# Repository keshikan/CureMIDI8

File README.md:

# USB-MIDI Interface (8IN/8OUT) for STM32 "CureMIDI8"

## Overview (概要)

This repository shows STM32F7 (ARM Cortex-M7) based  8IN/8OUT USB-MIDI Interface.
It is USB MIDI class-compliant, so you can add MIDI port without drivers(Windows, iOS, Android, etc...)

The USB-MIDI Class Driver is based on [mimuz-tuch](https://github.com/mimuz/mimuz-tuch) project (c) [D.F.Mac. @TripArts Music](https://github.com/tadfmac).

STM32F7を使用した、USB-MIDIインターフェースです。INを8系統、OUTを8系統実装しています。USB MIDI Classに対応するシステム(Windows, iOS, Android, etc.)に対し、ドライバレスでMIDI入出力ポートを追加できます。

USB MIDI Classドライバは、[D.F.Mac. @TripArts Music](https://github.com/tadfmac)氏作成の[ドライバ](https://github.com/mimuz/mimuz-tuch/tree/master/STM32)を元に、I/F部(usbd_midi_if.c/h)の改造を行っています。

## Specifications (特徴)

* High-Speed MCU (STM32F722VCT)
* USB MIDI class-compliant
* MIDI port: 8IN/8OUT
* MIDI buffer size: 2kB * (8IN+8OUT) = 32kB

## Building Information (ビルド方法)

### Making hardware

See [Schematic](./hardware/schematic.pdf), [KiCad Source](./hardware/kicad_source).
CureMIDI8 consist of a mainboard and a MIDI-IN board.

回路図は[こちら](./hardware/schematic.pdf).
CureMIDI8は、メイン基板(Mainboard)と、拡張基板(MIDI-IN board)に分かれています。

### Building software

Install [STM32CubeIDE](https://www.st.com/ja/development-tools/stm32cubeide.html), import [Project files](./software/CubeIDE_project/). If you have successfully imported, you can build the project without error and the binary file will be created in /CubeIDE_project/Debug/.

[STM32CubeIDE](https://www.st.com/ja/development-tools/stm32cubeide.html)をインストールし、[プロジェクトファイル](./software/CubeIDE_project/)をインポートして下さい。インポートに成功していれば、STM32CubeIDE上でプロジェクトをビルドするだけで、/SW4STM32_project/Debug/フォルダにバイナリファイルが生成されるはずです。

## How to Porting (ポーティング方法)

### CubeIDE Project (recommended)

Refer to [here](software/README.md). (written in Japanese)

[こちら](software/README.md)を参照して下さい。

### SW4STM32 Project

(Older Information)
Load CureMIDI8.ioc on [STM32CubeMX (Ver.5.0.1)](https://www.st.com/ja/development-tools/stm32cubemx.html), change the pin assignment, and generate code.
After code generation, copy usb device driver as described below. You can use ./click_after_code_generation.bat (in Windows).

(以下は古い情報です)
CureMIDI8.iocを[STM32CubeMX (Ver.5.0.1)](https://www.st.com/ja/development-tools/stm32cubemx.html)で読みこみ、ポートを適宜修正し、コード生成をして下さい。コードを生成後、./template下のUSBドライバを、下記の通り上書きして下さい。上書きは、./click_after_code_generation.batを実行してもOKです。

* ./template/\*.c => ./Src/\*.c
* ./template/\*.h => ./Inc/\*.h

## File Location (ファイルの場所)

* [Binary file for STM32F722](./software/bin/)
* [STM32CubeIDE + STM32CubeMX(6.1.1) Project file](./software/CubeIDE_Project/)
* [SW4STM32 + STM32CubeMX(5.0.1) Project file](./software/SW4STM32_project/)
* [Schematic](./hardware/schematic.pdf)

## NOTICE (注意)

### VID/PID

Vendor ID(VID) and Product ID(PID) in <usbd_desc.c> should be unique pair for each USB devices.
Default VID 0x1209 and PID 0x0001 is experimental IDs from [http://pid.codes](http://pid.codes) .When distributing or selling, you must get your own IDs, and change to your own IDs in order to avoid conflicting to other USB devices.

USBのVendor ID(VID)とProduct ID(PID)は、<usbd_desc.c>内に記述します。
デフォルトのVID(0x1209)/PID(0x0001)ペアは、[http://pid.codes](http://pid.codes)で定められている実験用IDです。そのため、本機器を配布したり販売したりする場合には、別途固有のIDペアを取得し、書き換えてご使用いただく必要があります。

## References (参考情報)

### MIDI specification

* [The Complete MIDI 1.0 Detailed Specification](https://www.midi.org/specifications/item/the-midi-1-0-specification) ([MIDI Association](https://www.midi.org/))
* [MIDI1.0規格書](http://amei.or.jp/midistandardcommittee/MIDI1.0.pdf) ([AMEI](http://amei.or.jp/))
* [MIDIの学習](http://www1.plala.or.jp/yuuto/midi/index.html) ([Laboratory "U"](http://www1.plala.or.jp/yuuto/top.html))

### USB-MIDI technical information

* [Universal Serial Bus Device Class Definition for MIDI Devices](http://www.usb.org/developers/docs/devclass_docs/midi10.pdf)
* [USBおよびUSB MIDIについて調べる](http://picmidi.seesaa.net/article/150728556.html) ([PICでMIDI！](http://picmidi.seesaa.net/))

## Copyrights (著作権)

* USB MIDI Class Driver by [D.F.Mac. @TripArts Music](http://ta-music.strikingly.com/)
* STM32 CubeF7 by [STMicroelectronics](https://www.st.com/en/embedded-software/stm32cubef7.html)

## Author (著者)

(c) 2019 Keshikan ( [Website](http://www.keshikan.net/),  [Twitter](https://twitter.com/keshinomi_88pro) )

## License (ライセンス)

* USB MIDI Class Driver: [CC BY 4.0](https://creativecommons.org/licenses/by/4.0/)
* STM32 CubeF7: BSD-3-Clause based.
* Other Codes, Hardware, Schematic: [GPLv3](https://www.gnu.org/licenses/gpl-3.0.html)

See also [LICENSE.md](./LICENSE.md)

## Update History (更新履歴)

* (2021/02/14)
  * Added STM32CubeIDE(1.5.1) + CubeMX(6.1.1) Project.
* (2019/01/14)
  * Initial Release.

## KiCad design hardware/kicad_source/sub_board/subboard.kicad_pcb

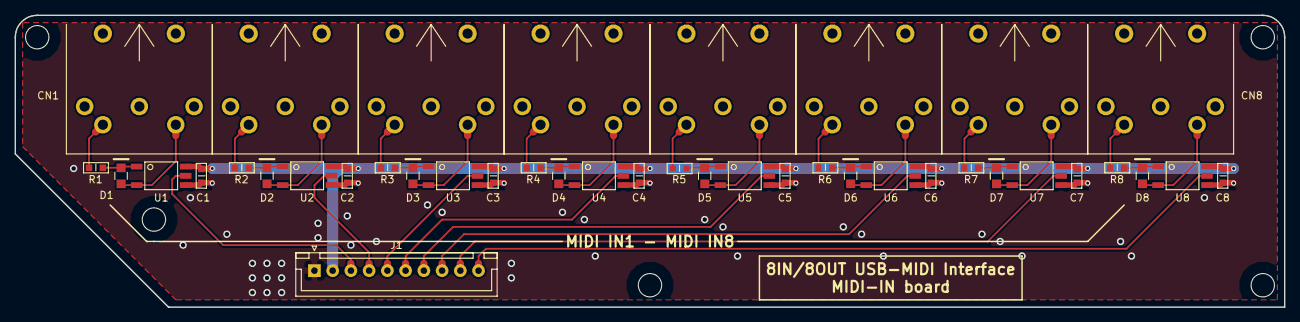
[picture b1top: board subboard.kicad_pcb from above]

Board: 2 copper layers, 174.0 x 40.0 mm, 41 parts (0 on the bottom side), 34 nets.

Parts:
C1, C2, C3, C4, C5, C6, C7, C8: 0.1μF; SMD_0603(1608)
CN1, CN2, CN3, CN4, CN5, CN6, CN7, CN8: DIN_5; DIN_5P_MIDI
D1, D2, D3, D4, D5, D6, D7, D8: D_Small; SMD_0805(2012)_polar
J1: Conn_01x10; JST_XH_B10B-XH-A_10x2.50mm_Straight
R1, R2, R3, R4, R5, R6, R7, R8: 220; SMD_0603(1608)
U1, U2, U3, U4, U5, U6, U7, U8: TLP2361; 11-4L1S(TLP2361)

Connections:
IN_1: J1.3, U1.5
IN_2: J1.4, U2.5
IN_3: J1.5, U3.5
IN_3V3: C1.1, C2.1, C3.1, C4.1, C5.1, C6.1, C7.1, C8.1, J1.2, U1.6, U2.6, U3.6, U4.6, U5.6, U6.6, U7.6, U8.6
IN_4: J1.6, U4.5
IN_5: J1.7, U5.5
IN_6: J1.8, U6.5
IN_7: J1.9, U7.5
IN_8: J1.10, U8.5
IN_GND: C1.2, C2.2, C3.2, C4.2, C5.2, C6.2, C7.2, C8.2, J1.1, U1.4, U2.4, U3.4, U4.4, U5.4, U6.4, U7.4, U8.4
unnamed: CN1.4, R1.1
unnamed: CN1.5, D1.2, U1.3
unnamed: CN2.4, R2.1
unnamed: CN2.5, D2.2, U2.3
unnamed: CN3.4, R3.1
unnamed: CN3.5, D3.2, U3.3
unnamed: CN4.4, R4.1
unnamed: CN4.5, D4.2, U4.3
unnamed: CN5.4, R5.1
unnamed: CN5.5, D5.2, U5.3
unnamed: CN6.4, R6.1
unnamed: CN6.5, D6.2, U6.3
unnamed: CN7.4, R7.1
unnamed: CN7.5, D7.2, U7.3
unnamed: CN8.4, R8.1
unnamed: CN8.5, D8.2, U8.3
unnamed: D1.1, R1.2, U1.1
unnamed: D2.1, R2.2, U2.1
unnamed: D3.1, R3.2, U3.1
unnamed: D4.1, R4.2, U4.1
unnamed: D5.1, R5.2, U5.1
unnamed: D6.1, R6.2, U6.1
unnamed: D7.1, R7.2, U7.1
unnamed: D8.1, R8.2, U8.1

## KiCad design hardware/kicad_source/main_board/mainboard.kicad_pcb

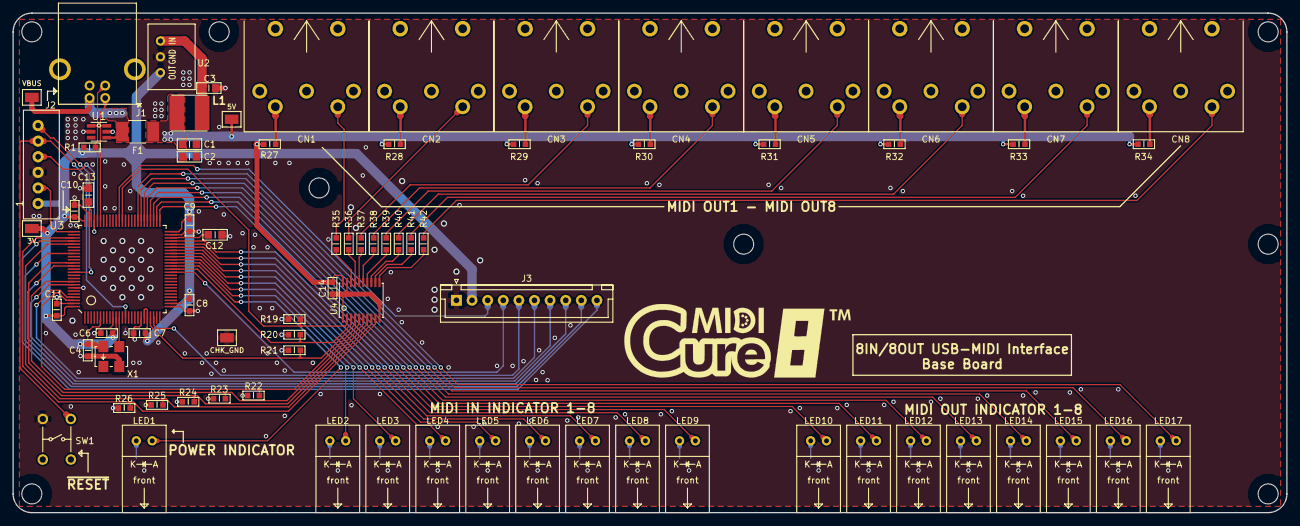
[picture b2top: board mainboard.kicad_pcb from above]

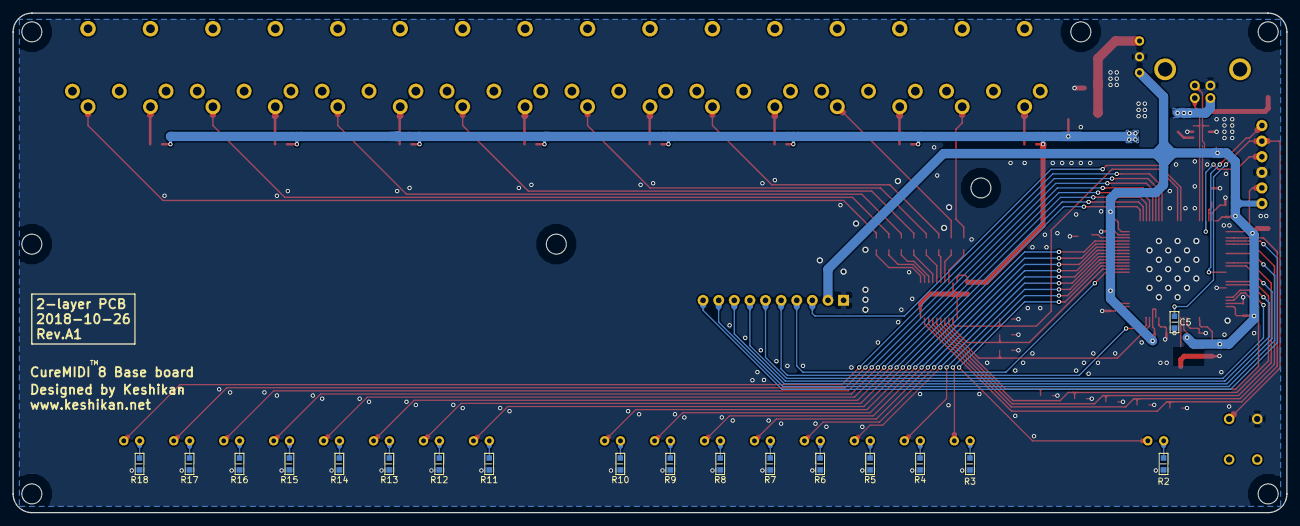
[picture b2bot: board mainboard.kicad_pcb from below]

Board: 2 copper layers, 204.0 x 80.0 mm, 96 parts (18 on the bottom side), 88 nets.

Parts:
C1, C2, C3, C12, C13: 4.7μF; SMD_0805(2012)
C4, C5, C6, C7, C8, C9, C10, C11, C14: 0.1μF; SMD_0603(1608)
CN1, CN2, CN3, CN4, CN5, CN6, CN7, CN8: DIN_5; DIN_5P_MIDI
F1: PolySW 0.35A; miniSMDC030F
J1: USB_B; USB_B_F
J2: CONN_01X06; XH-6P-TOP
J3: Conn_01x10; JST_XH_B10B-XH-A_10x2.50mm_Straight
L1: 10μH; Wurth_Elektronik_74477410
LED1, LED2, LED3, LED4, LED5, LED6, LED7, LED8, LED9, LED10, LED11, LED12, LED13, LED14, LED15, LED16, LED17: LED_Small; LEDSpacer_1low
P1: VBUS; CHK_Terminal_SMD
P2: 5V; CHK_Terminal_SMD
P3: 3V; CHK_Terminal_SMD
P4: CHK_GND; CHK_Terminal_SMD
R1, R2, R3, R4, R5, R6, R7, R8, R9, R10, R11, R12, R13, R14, R15, R16, R17, R18: 4.7k; SMD_0603(1608)
R19, R20, R21, R22, R23, R24, R25, R26: 100k; SMD_0603(1608)
R27, R28, R29, R30, R31, R32, R33, R34, R35, R36, R37, R38, R39, R40, R41, R42: 220; SMD_0603(1608)
SW1: SW_PUSH_SMALL_H; Tactile_Switches_2by2
U1: ESDA6V1BC6; SOT23-6L
U2: M78AR033-0.5
U3: STM32F722VCTx; LQFP100_14x14_STM32
U4: 74VHCV541FT; TSSOP20B
X1: SG5032CAN 8MHz; SG5032

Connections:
+3V3: C4.1, C6.1, C7.1, C8.1, C9.1, C10.1, C11.1, J2.1, J3.2, P3.1, R1.2, U2.3, U3.6, U3.11, U3.20, U3.21, U3.27, U3.50, U3.75, U3.100, X1.4
+5V: C1.1, C2.1, C14.1, F1.1, L1.1, P2.1, R27.1, R28.1, R29.1, R30.1, R31.1, R32.1, R33.1, R34.1, U4.20
GND: C1.2, C2.2, C3.2, C4.2, C5.2, C6.2, C7.2, C8.2, C9.2, C10.2, C11.2, C12.2, C13.2, C14.2, J1.4, J2.3, J3.1, P4.1, R2.1, R3.1, R4.1, R5.1, R6.1, R7.1, R8.1, R9.1, R10.1, R11.1, R12.1, R13.1, R14.1, R15.1, R16.1, R17.1, R18.1, R19.1, R20.1, R21.1, R22.1, R23.1, R24.1, R25.1, R26.1, SW1.1, U1.2, U1.5, U2.2, U3.10, U3.19, U3.26, U3.49, U3.74, U3.94, U3.99, U4.1, U4.10, U4.19, X1.2
MIDI_IN_1: J3.3, U3.64
MIDI_IN_2: J3.4, U3.37
MIDI_IN_3: J3.5, U3.23
MIDI_IN_4: J3.6, U3.97
MIDI_IN_5: J3.7, U3.93
MIDI_IN_6: J3.8, U3.87
MIDI_IN_7: J3.9, U3.83
MIDI_IN_8: J3.10, U3.79
MIDI_OUT_1: R19.2, U3.63, U4.2
MIDI_OUT_2: R20.2, U3.38, U4.3
MIDI_OUT_3: R21.2, U3.22, U4.4
MIDI_OUT_4: R22.2, U3.98, U4.5
MIDI_OUT_5: R23.2, U3.92, U4.6
MIDI_OUT_6: R24.2, U3.86, U4.7
MIDI_OUT_7: R25.2, U3.80, U4.8
MIDI_OUT_8: R26.2, U3.78, U4.9
NRST: C5.1, J2.5, SW1.2, U3.14
unnamed: C3.1, L1.2, U2.1
unnamed: C12.1, U3.48
unnamed: C13.1, U3.73
unnamed: CN1.4, R27.2
unnamed: CN1.5, R35.2
unnamed: CN2.4, R28.2
unnamed: CN2.5, R36.2
unnamed: CN3.4, R29.2
unnamed: CN3.5, R37.2
unnamed: CN4.4, R30.2
unnamed: CN4.5, R38.2
unnamed: CN5.4, R31.2
unnamed: CN5.5, R39.2
unnamed: CN6.4, R32.2
unnamed: CN6.5, R40.2
unnamed: CN7.4, R33.2
unnamed: CN7.5, R41.2
unnamed: CN8.4, R34.2
unnamed: CN8.5, R42.2
unnamed: LED1.1, R2.2
unnamed: LED1.2, U3.39
unnamed: LED2.1, R3.2
unnamed: LED2.2, U3.40
unnamed: LED3.1, R4.2
unnamed: LED3.2, U3.41
unnamed: LED4.1, R5.2
unnamed: LED4.2, U3.42
unnamed: LED5.1, R6.2
unnamed: LED5.2, U3.43
unnamed: LED6.1, R7.2
unnamed: LED6.2, U3.44
unnamed: LED7.1, R8.2
unnamed: LED7.2, U3.45
unnamed: LED8.1, R9.2
unnamed: LED8.2, U3.46
unnamed: LED9.1, R10.2
unnamed: LED9.2, U3.47
unnamed: LED10.1, R11.2
unnamed: LED10.2, U3.51
unnamed: LED11.1, R12.2
unnamed: LED11.2, U3.52
unnamed: LED12.1, R13.2
unnamed: LED12.2, U3.53
unnamed: LED13.1, R14.2
unnamed: LED13.2, U3.54
unnamed: LED14.1, R15.2
unnamed: LED14.2, U3.55
unnamed: LED15.1, R16.2
unnamed: LED15.2, U3.56
unnamed: LED16.1, R17.2
unnamed: LED16.2, U3.57
unnamed: LED17.1, R18.2
unnamed: LED17.2, U3.58
unnamed: R35.1, U4.18
unnamed: R36.1, U4.17
unnamed: R37.1, U4.16
unnamed: R38.1, U4.15
unnamed: R39.1, U4.14
unnamed: R40.1, U4.13
unnamed: R41.1, U4.12
unnamed: R42.1, U4.11
unnamed: U3.12, X1.3
SWCLK: J2.2, U3.76
SWDIO: J2.4, U3.72
SWO: J2.6, U3.89
USBD_N: J1.2, U1.6, U3.70
USBD_P: J1.3, R1.1, U1.1, U3.71
VBUS: F1.2, J1.1, P1.1, U1.4

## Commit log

2019-01-14 Modified circuit: R19-26(Main board) must be pulled-up.
2019-01-16 Add Japanese description to README.md
2019-06-14 Added KiCad source files.
2021-02-13 Added CubeIDE project
2021-02-14 little modify
2021-02-14 Modified README
2021-02-14 Modified readme: works with STM32H750VB
2021-02-14 Modified readme (usage)
